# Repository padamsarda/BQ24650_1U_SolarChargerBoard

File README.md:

# BQ24650 1U SolarChargerBoard 

A dev/eval board for the **TI BQ24650** standalone solar battery charger IC. The board was developed to provide a simpler and more custom platform for evaluating the BQ24650 for ANANTSAT-I(1u mission) after the standard eval-board proved unsuitable for the intended testing. It implements the complete synchronous buck battery charger power stage required by the charger IC, while exposing adjustable potentiometers for configuring the battery regulation voltage and the constant-voltage MPPT operating point, also has LEDs for the BQ2460 status pins. Temp sense pin is available for using external thermocoupler/thermistor.

### Board at a glance

| Item              | Description                                          |
| ----------------- | ---------------------------------------------------- |
| Charger IC        | Texas Instruments BQ24650                            |
| MPPT              | Adjustable constant-voltage MPPT using potentiometer |
| Input Source      | Solar panel                                          |
| Charge Voltage    | Adjustable using potentiometer                       |
| Power Stage       | External NMOS MOSFETs and inductor                   |
| Monitoring        | Multiple test points for evaluation                  |
| Temperature Input | TS connector for battery temperature sensing         |

## Schematic

## PCB

## Key Components

| Reference  | Part           | Function                              |
| ---------- | -------------- | ------------------------------------- |
| U1         | BQ24650        | Solar battery charger controller      |
| Q1, Q2, Q3 | NMOS MOSFET    | Synchronous buck power stage, act as switch for shut down          |
| L1         | Inductor       | Buck converter        |
| D2         | Schottky Diode | Power path/freewheeling diode         |
| RV1        | Potentiometer  | Battery regulation voltage adjustment |
| RV2        | Potentiometer  | MPPT voltage adjustment               |
| D1         | Power diode    | Input protection / power path         |

## Connectors & I/O

| Reference | Interface   | Description                           |
| --------- | ----------- | ------------------------------------- |
| J1        | CE/MPPSET   | Charger enable and MPPT configuration |
| J2        | Solar+      | Solar panel input                     |
| J3        | Solar−      | Solar panel return                    |
| J4        | BATT+       | Battery positive connection           |
| J5        | BATT−       | Battery return                        |
| J6        | TS          | Battery temperature sensing input     |
| TP1–TP9   | Test Points | Circuit measurement and debugging     |

Designed and developed as part of **Team Anant**.

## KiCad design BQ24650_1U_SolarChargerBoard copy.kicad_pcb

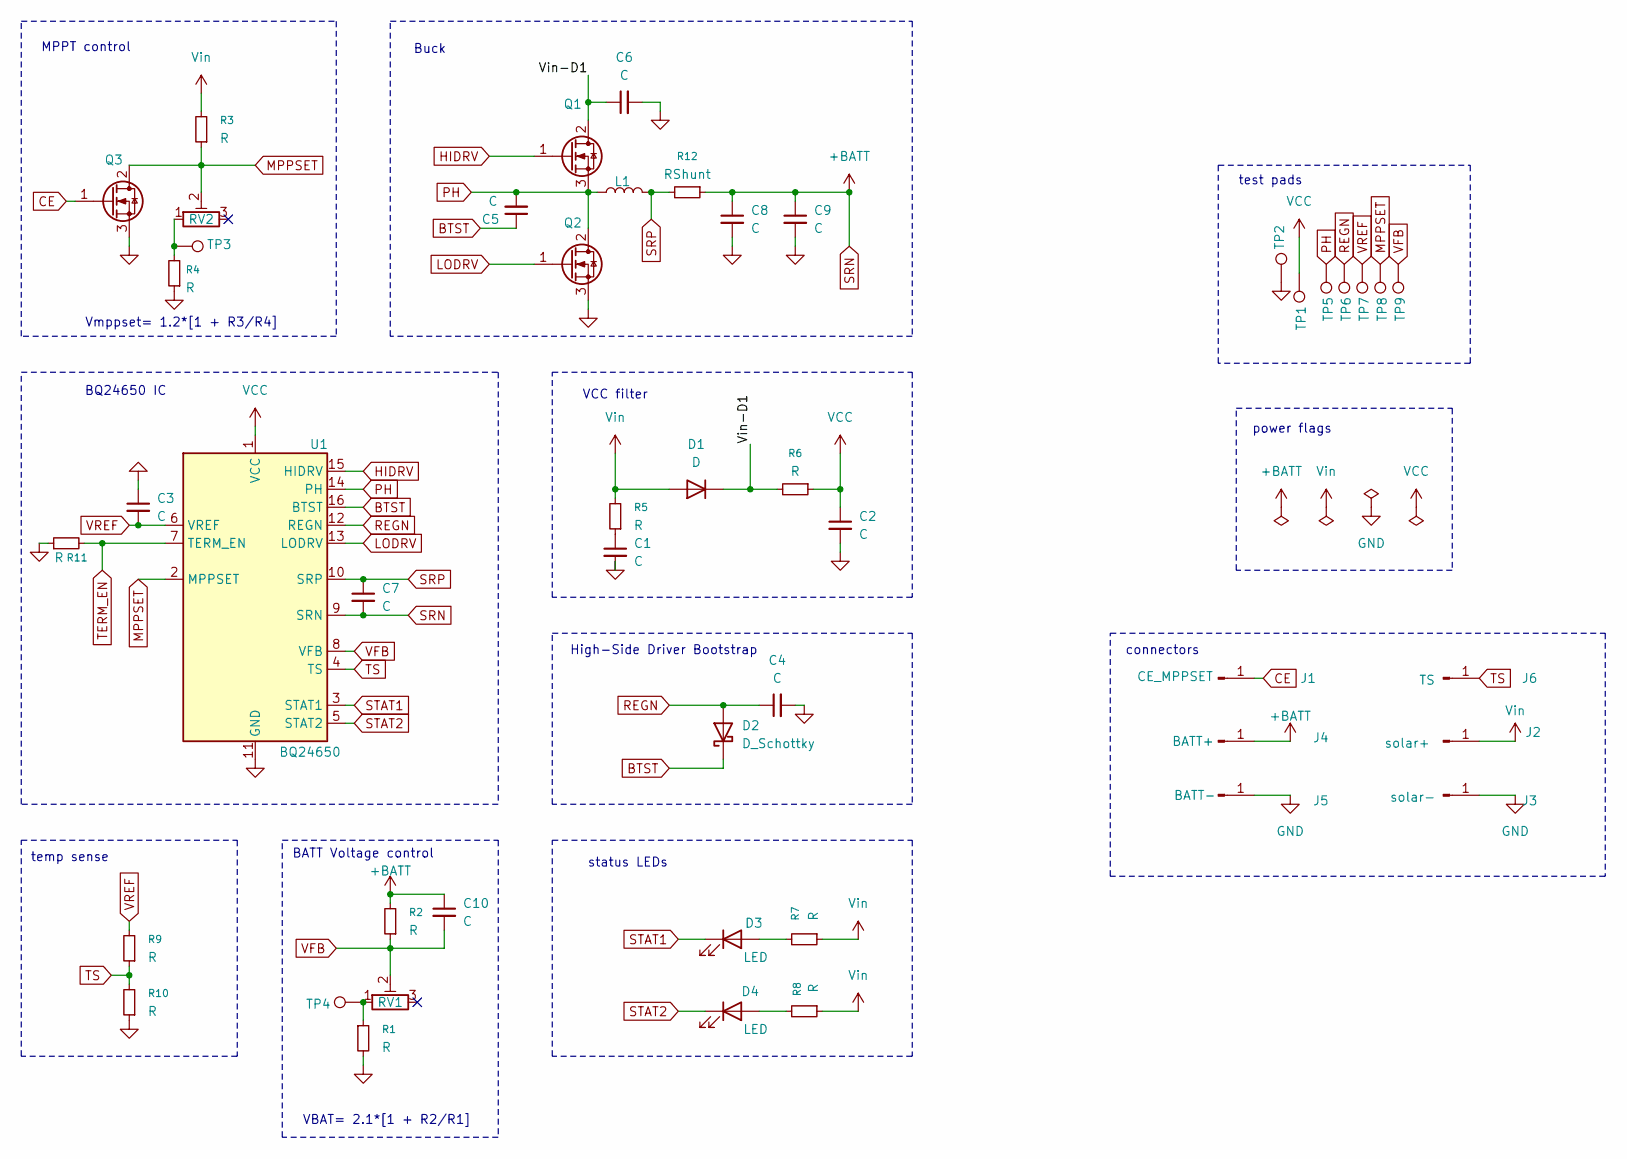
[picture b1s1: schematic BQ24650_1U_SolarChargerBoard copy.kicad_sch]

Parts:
C1, C2, C3, C4, C5, C6, C7, C8, C9: C; C_0805_2012Metric
C10: C; C_0603_1608Metric
D1: D; D_PowerDI-5
D2: D_Schottky; SOT-23
D3, D4: LED; C_0603_1608Metric
J1: CE_MPPSET; PinHeader_1x01_P2.54mm_Vertical
J2: solar+; PinHeader_1x01_P2.54mm_Vertical
J3: solar-; PinHeader_1x01_P2.54mm_Vertical
J4: BATT+; PinHeader_1x01_P2.54mm_Vertical
J5: BATT-; PinHeader_1x01_P2.54mm_Vertical
J6: TS; PinHeader_1x01_P2.54mm_Vertical
L1: L; L_Vishay_IHLP-2525
Q1, Q2: Q_NMOS_GDS; PowerPAK_SO-8_Dual
Q3: Q_NMOS_GDS; SOT-23
R1, R2, R3, R4, R7, R8, R9, R10, R11: R; R_0402_1005Metric
R5: R; R_2512_6332Metric
R6: R; R_1206_3216Metric
R12: RShunt; R_2512_6332Metric
RV1, RV2: R_Potentiometer_Trim; Potentiometer_Bourns_3296W_Vertical
TP1, TP2, TP3, TP4, TP5, TP6, TP7, TP8, TP9: TestPoint; TestPoint_Pad_D1.5mm
U1: BQ24650; Texas_RVA_VQFN-16-1EP_3.5x3.5mm_P0.5mm_EP2.14x2.14mm_Therma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

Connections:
/Vin-D1: C6.1, D1.1 (K), Q1.2 (D), R6.2
BTST: C5.1, D2.1 (K), U1.16 (BTST)
CE: J1.1 (Pin_1_1), Q3.1 (G)
GND: C1.2, C2.2, C3.1, C4.2, C6.2, C8.2, C9.2, J3.1 (Pin_1_1), J5.1 (Pin_1_1), Q2.3 (S), Q3.3 (S), R1.2, R4.1, R10.1, R11.1, TP2.1 (1_1), U1.11 (GND), U1.17 (GND)
HIDRV: Q1.1 (G), U1.15 (HIDRV)
LODRV: Q2.1 (G), U1.13 (LODRV)
MPPSET: Q3.2 (D), R3.1, RV2.2, TP8.1 (1_1), U1.2 (MPPSET)
unnamed: C1.1, R5.1
unnamed: D3.2 (A), R7.2
unnamed: D4.2 (A), R8.2
unnamed: R1.1, RV1.1, TP4.1 (1_1)
unnamed: R4.2, RV2.1, TP3.1 (1_1)
PH: C5.2, L1.1, Q1.3 (S), Q2.2 (D), TP5.1 (1_1), U1.14 (PH)
REGN: C4.1, D2.2 (A), TP6.1 (1_1), U1.12 (REGN)
SRN: C7.2, C8.1, C9.1, C10.1, J4.1 (Pin_1_1), R2.2, R12.1, U1.9 (SRN)
SRP: C7.1, L1.2, R12.2, U1.10 (SRP)
STAT1: D3.1 (K), U1.3 (STAT1)
STAT2: D4.1 (K), U1.5 (STAT2)
TERM_EN: R11.2, U1.7 (TERM_EN)
TS: J6.1 (Pin_1_1), R9.1, R10.2, U1.4 (TS)
VCC: C2.1, R6.1, TP1.1 (1_1), U1.1 (VCC)
VFB: C10.2, R2.1, RV1.2, TP9.1 (1_1), U1.8 (VFB)
VREF: C3.2, R9.2, TP7.1 (1_1), U1.6 (VREF)
Vin: D1.2 (A), J2.1 (Pin_1_1), R3.2, R5.2, R7.1, R8.1

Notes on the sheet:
VBAT= 2.1*[1 + R2/R1]
BATT Voltage control
status LEDs
power flags
Buck
Vmppset= 1.2*[1 + R3/R4]
High-Side Driver Bootstrap
connectors
VCC filter
MPPT control
BQ24650 IC
temp sense
test pads

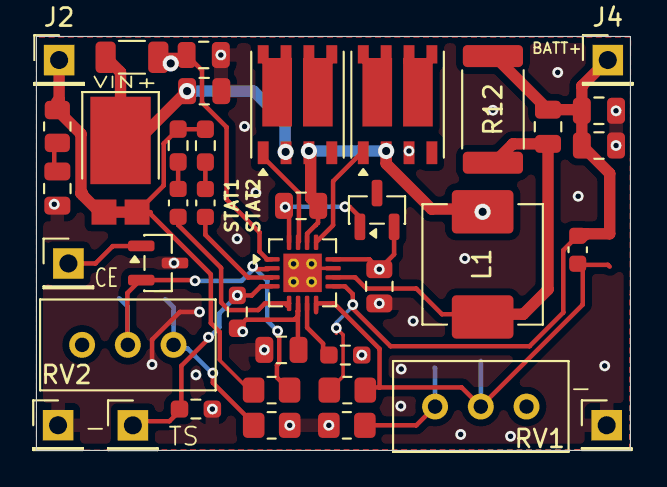
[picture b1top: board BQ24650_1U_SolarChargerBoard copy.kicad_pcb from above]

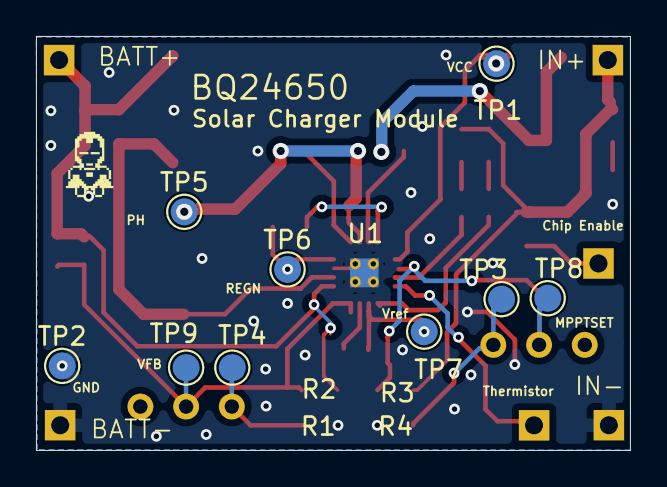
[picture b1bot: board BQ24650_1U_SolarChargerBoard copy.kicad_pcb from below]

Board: 2 copper layers, 33.0 x 23.0 mm, 48 parts (9 on the bottom side), 24 nets.

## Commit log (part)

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2026-06-23 Initial BQ24650 evaluation board schematic
2026-06-23 Add .gitignore and remove generated KiCad files
2026-06-24 small changes
2026-06-24 Assigned footprints
2026-06-25 decided Front and back components
2026-06-27 finishing touches
